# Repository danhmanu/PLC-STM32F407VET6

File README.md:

# PLC STM32F407VET6 – Modbus TCP – 16 DO transistor – 10 AI

Mạch nguyên lý KiCad 10 cho bộ PLC: điều khiển qua LAN bằng **Modbus TCP** (module W5500 Lite), nạp code qua **USB‑C (CH340C)**, 16 ngõ ra transistor cách ly quang, 10 ngõ vào analog **4–20mA**.

## Cấu trúc thư mục

| Đường dẫn | Nội dung |
|---|---|
| `kicad/PLC_STM32_Modbus.kicad_pro` | Project KiCad (mở file này) |
| `kicad/*.kicad_sch` | 6 trang mạch con (xem bảng dưới) |
| `kicad/PLC_STM32_Modbus.pdf` | Bản in PDF toàn bộ mạch |
| `kicad/BOM.csv` | Danh sách linh kiện (gom theo giá trị + footprint) |
| `kicad/erc.rpt` | Báo cáo ERC |
| `kicad/PLC_STM32_Modbus.kicad_pcb` | Mạch in 2 lớp 100×80mm |
| `kicad/fab/` | File sản xuất: Gerber + khoan (zip), file gắp đặt 2 mặt, PDF từng lớp, ảnh 3D |
| `gen/design.py`, `gen/kisch.py` | Script sinh mạch nguyên lý – sửa ở đây rồi chạy lại `sh gen/run.sh` |
| `gen/pcb.py`, `gen/finish.py`, `gen/fab.sh` | Script đặt linh kiện, nạp kết quả đi dây + đổ đồng, xuất file sản xuất |

> ⚠️ Các file `.kicad_sch` được **sinh tự động**. Nếu bạn sửa trực tiếp trong KiCad thì **đừng** chạy lại `gen/run.sh`, vì script sẽ ghi đè lên các file đó.

## Các trang mạch

| Trang | Nội dung chính |
|---|---|
| **Nguồn 24VDC** | PTC MF‑MSMF050 (0.5A/60V) → diode chống ngược SS110 → TVS SMBJ33CA → cuộn lọc common‑mode TDK ACM7060 → ferrite 3A + 47µF/10µF → **+24V**. Buck **LMR16006Y** (vào tới 60V) → 5V. Diode OR với VBUS của USB → **AMS1117‑3.3** → +3V3. Ferrite tách riêng **+3.3VA** cho ADC |
| **MCU** | STM32F407VET6, thạch anh 8MHz, **REF3030 (3.000V) làm VREF+**, nút RESET/BOOT, cổng SWD 10 chân, LED RUN/ERR |
| **USB nạp code** | USB‑C, USBLC6 chống tĩnh điện, polyfuse 500mA, **CH340C → USART1** (cổng bootloader của STM32), mạch tự vào bootloader bằng DTR/RTS (2×MMBT3904 + MMBT3906), jumper AUTO‑BOOT |
| **Ethernet** | **Module W5500 Lite** (J401, có sẵn W5500 + thạch anh + biến áp + RJ45), cắm qua 2 hàng socket 1×6. Trên board chỉ còn tụ 10µF + 100nF cho 3V3 module và 2 trở kéo lên 10k cho INT/RST – Modbus TCP |
| **16 ngõ ra transistor** | Mỗi kênh: opto **PC817 (SMD‑4, cách ly 5000 Vrms)** → **MOSFET DMN6075S (60V/2.5A)**, diode dập SS16, LED báo phía tải. Kiểu ngõ ra **sink (NPN)**: tải đấu giữa V+ và Yn |
| **10 ngõ vào analog (chỉ 4–20mA)** | Mỗi kênh: TVS SMF5.0CA, **shunt 120Ω 0.1% 25ppm**, lọc RC 4.7k/100nF vào ADC (không có cầu chì từng kênh). Cầu đấu J703 cấp nguồn 24V nuôi cảm biến 2 dây, qua PTC F711 **0.5A/60V (MF‑MSMF050‑2, gói 1812)** |

## Cách đọc sơ đồ

**Kiểu vẽ:**
- **Nối trong cùng một trang:** vẽ bằng **dây thật**. Mỗi net có một nhãn tên đặt trên dây (VIN_P, BUCK_SW, OSC_IN…) để tìm kiếm.
- **Tín hiệu đi sang trang khác:** dùng **nhãn global** (DOx, AIx_ADC, ETH_*, UART1_*, NRST, BOOT0…).
- **GND, +3V3, +24V…:** dùng power symbol.
- **Một số net vẫn giữ dạng nhãn**, vì nếu kéo dây thật sẽ phải băng ngang cả trang:
  - Hai rail ngõ ra **V24_OUT / COM_OUT** (37–53 điểm nối).
  - Một số đường **Yn** ra cầu đấu J501/J502.

**Ghi chú trên sơ đồ:**
- Ghi chú màu xanh (font Arial, tiếng Việt có dấu) đặt **ngay cạnh linh kiện / khối mà nó giải thích** (vị trí được tìm tự động để không đè lên ký hiệu, dây, nhãn):
  - Mỗi khối mạch có một tiêu đề in đậm nêu tác dụng của khối.
  - Mỗi linh kiện hoặc nhóm linh kiện có ghi chú ngắn về vai trò của nó.
  - Với 16 kênh ngõ ra và 10 kênh analog (giống nhau), ghi chú chi tiết đặt ở kênh đầu tiên.
  - **Cách tính giá trị**: dòng LED, cầu chia gate MOSFET, gợn dòng/gợn áp bộ buck, tụ tải thạch anh, điện trở shunt 4–20mA, tần số cắt bộ lọc RC, trở phối hợp Ethernet…
- Trang tổng quan (root) tóm tắt toàn hệ thống.
- Nội dung ghi chú nằm trong `gen/notes.py`; sửa ở đó rồi chạy `sh gen/run.sh` để cập nhật.

**Tìm nhanh một net trong Eeschema:**
- Bấm vào dây hoặc nhãn rồi nhấn **`** (phím dấu huyền) để tô sáng cả net.
- **View → Panels → Net Navigator** để xem danh sách mọi chân của net.
- **Ctrl+F** để tìm theo tên.

**Sinh lại sơ đồ:**
- Chạy `sh gen/run.sh`. Bộ tự đi dây nằm trong `gen/schroute.py`.
- Sau đó cập nhật liên kết PCB:
  1. Xuất netlist: `kicad-cli sch export netlist --format kicadsexpr -o gen/plc.net kicad/PLC_STM32_Modbus.kicad_sch`
  2. Chạy `gen/relink.py`.
- Đường dây trên PCB được giữ nguyên.

## Gán chân STM32F407VET6

| Chức năng | Chân |
|---|---|
| DO1…DO16 | PE1, PE0, PB9, PB8, PB7, PB6, PB5, PB4, PD7, PD6, PD5, PD4, PD3, PD2, PD1, PD0 (các chân ở cạnh trên của LQFP, hướng về khối ngõ ra để dễ đi dây) |
| AI1…AI10 | PA0, PA1, PA2, PA3, PC0, PC1, PC2, PC3, PC4, PC5 (ADC1, 12‑bit) |
| Module W5500 Lite (SPI2, tối đa 21MHz) | PB12 = CS, PB13 = SCK, PB14 = MISO, PB15 = MOSI, PD8 = RST, PD9 = INT |
| USB/CH340C (USART1) | PA9 = TX, PA10 = RX |
| SWD | PA13 = SWDIO, PA14 = SWCLK, PB3 = SWO |
| LED | PD12 = RUN, PD13 = ERR |
| Còn trống | PA4–PA8, PA11, PA12, PA15, PB0, PB1, PB10, PB11, PC6–PC15, PD10, PD11, PD14, PD15, PE2–PE15 (đã đánh dấu NC) |

## Ngõ vào analog 4–20mA – công thức đổi

- Shunt 120Ω nối thẳng vào ADC qua lọc RC (không còn cầu chia áp): `Vadc = I × 120Ω`, VREF = 3.000V.
  - 4mA → 0.48V, 20mA → 2.40V, 24mA → 2.88V.
  - Dải 4–20mA chiếm khoảng 2600 mức ADC.
  - Phát hiện được dòng lỗi theo NAMUR: < 3.8mA (đứt dây) và > 20.5mA.
- **Sụt áp trên tải ≈ 2.4V ở 20mA.** Cảm biến 2 dây cấp 24V còn khoảng 21V để hoạt động.
- **Đấu dây cảm biến:**
  - **2 dây (loop‑powered):** 24V loop (J703) → (+) cảm biến → (−) cảm biến → AIn (J701).
  - **4 dây:** ngõ ra mA của cảm biến → AIn; chân 0V của cảm biến → GND (J703).
- **Firmware:** `I(mA) = raw / 4095 × 3000 / 120`. Nên hiệu chuẩn offset/gain cho từng kênh và lưu vào Holding Register.
- **Bảo vệ:** TVS 5V kẹp xung/quá áp; trở 4.7k giới hạn dòng vào chân ADC ở khoảng 1mA.
- ⚠️ **Không có cầu chì từng kênh:** nếu đấu nhầm 24V thẳng vào chân AI, dòng 24V/120Ω = 200mA (4.8W) sẽ **cháy shunt 120Ω và TVS** của kênh đó. Chân ADC vẫn an toàn. Kiểm tra kỹ dây trước khi cấp điện.

## Ngõ ra transistor

- Phía tải có nguồn riêng: cấp 24V vào **V+ / COM** trên cầu đấu J501/J502 (chân 2 = V+, chân 1 = COM; chân 10…3 = Y1…Y8).
  - Nguồn này **cách ly** với mạch logic qua opto.
  - Nếu không cần cách ly, có thể nối chung với nguồn 24V của board.
- Khi kênh ON, gate MOSFET ≈ ½·V+ (≈ 12V). Dòng tối đa mỗi kênh khoảng 2A (giới hạn bởi tản nhiệt SOT‑23 và độ rộng đường mạch). Nên giới hạn tổng dòng mỗi nhóm 8 kênh ≤ 4A.

## Nạp chương trình qua USB

1. Cắm USB‑C. Không cần cấp 24V: board tự lấy nguồn 5V từ USB.
2. **Tự động** (cắm jumper AUTO‑BOOT JP301): phần mềm nạp điều khiển hai đường DTR/RTS theo trình tự sau (giống esptool):
   - RTS = 1, DTR = 0 → MCU bị reset.
   - RTS = 0, DTR = 1 → nhả reset trong khi BOOT0 = 1 → MCU vào bootloader UART.
   - Thả cả hai.
   - Có thể dùng `stm32flash` với tùy chọn `-i` (chuỗi GPIO DTR/RTS), hoặc script Python + pyserial.
3. **Thủ công**: giữ **BOOT**, bấm rồi nhả **RESET**, sau đó nhả BOOT. Tiếp theo nạp bằng **STM32CubeProgrammer** (UART) hoặc Arduino IDE (STM32duino, upload method “Serial”).
4. Cổng SWD (ST‑Link) để debug.

## Bảng địa chỉ Modbus TCP gợi ý (cổng 502)

| Vùng | Địa chỉ | Nội dung |
|---|---|---|
| Coils | 00001–00016 | DO1–DO16 |
| Input Registers | 30001–30010 | AI1–AI10 (raw hoặc ×100 đơn vị kỹ thuật) |
| Holding Registers | 40001+ | IP/mask/gateway, chế độ V/mA từng kênh, hệ số hiệu chuẩn, timeout an toàn cho ngõ ra |

⚠️ Modbus TCP **không có mã hóa hay xác thực**. Nếu muốn điều khiển qua Internet, hãy đi qua VPN (WireGuard/Tailscale). Không mở thẳng port 502 trên router.

## Mạch in (PCB) 2 lớp – 120 × 90 mm

**Bố trí** (nhìn từ mặt trên):
- **Cạnh trên – phía tải (cách ly):** cầu đấu ngõ ra J501/J502, bước 3.81mm. Từ trái sang phải: Y1…Y8, V+, COM | Y9…Y16, V+, COM. Ở giữa hai cầu đấu là TVS + tụ lọc nguồn relay.
- **Cạnh dưới:** J701 (AI1…AI10, 4–20mA), J703 (24V loop ×3, GND ×3), J101 (24VDC IN: +, −).
- **Cạnh trái:** USB‑C nạp code. **Cạnh phải:** module W5500 Lite, cổng LAN chĩa ra ngoài mép board (nhô ~2.5mm).
- **Bên trong:** MCU ở giữa, module Ethernet bên phải, khối nguồn ở góc dưới phải (dịch xuống 1.2mm để nhường chỗ cho module), analog ở góc dưới trái. 4 lỗ bắt vít M3 ở 4 góc.
- **Mặt dưới** chỉ có tụ/trở nhỏ (tụ lọc ngay dưới chân nguồn IC, cầu chia analog, cổng SWD) → cần **lắp ráp SMT 2 mặt**.

### Lắp module W5500 Lite

- Hàn lên board **2 hàng socket cái 1×6 (bước 2.54mm), cách nhau 20.32mm**. Module hàn header đực **chân hướng xuống** rồi cắm vào socket.
- Hướng cắm: **cổng LAN hướng ra mép phải** của board, chân vuông (pin 1 = GND) theo silkscreen.
- Dưới thân module (mặt dưới board) có C401 10µF, C402 100nF (lọc 3V3) và R401/R402 10k (kéo lên INT/RST).
- Nối dây module ↔ STM32: MOSI→PB15, SCLK→PB13, CS→PB12, MISO→PB14, INT→PD9, RST→PD8, 3V3, GND. Chân NC để trống.

### Cách ly ngõ ra – dùng với relay ngoài có nguồn riêng

- **Không cần thêm bộ cách ly.** Mỗi kênh đã có opto PC817 (cách ly 5000 Vrms) giữa MCU và MOSFET.
- **Thông số PC817 trong mạch:**
  - Dòng LED ≈ 4.5mA (3.3V qua 470Ω). Với CTR tối thiểu 50%, transistor của opto dẫn được ≥ 2.2mA, trong khi mạch kích gate chỉ cần ≈ 1.2mA.
  - Vceo của PC817 là 35V, nên **nguồn relay tối đa 30V**.
  - Nên dùng PC817 có phân hạng CTR (B/C) cho chắc chắn.
- **Footprint:** SMDIP‑4 W9.53mm (bản chân cánh, mã đuôi "S", ví dụ PC817XNNSZ0F hoặc EL817S). Mỗi kênh một opto, đặt vắt qua rãnh cách ly; khoảng cách giữa hai hàng pad ≈ 7.5mm.
- **Đấu nối:** nguồn relay **+ → V+**, **0V → COM**, cuộn relay đấu giữa **V+** và **Yn**. Diode dập SS16 đã có sẵn trên board.
- **Điện áp relay hỗ trợ: 12–30V** (gate MOSFET được phân áp ≈ ½·V+). Relay 5V không dùng được với bộ trở hiện tại.
- **Ngõ ra kiểu sink (NPN).** Nếu dùng module relay có sẵn mạch kích, chọn loại kích mức thấp / NPN.
- **Trên PCB:**
  - Có **rãnh cách ly 2.4mm** chạy ngang dưới thân 16 opto. Trong rãnh không có dây, via hay đồng trên cả 2 lớp.
  - Phía tải đổ đồng **COM_OUT**, phía logic đổ đồng **GND**. Chỉ opto bắc qua rãnh.
  - **Đừng nối COM với GND của board.** Nếu nối thì mất cách ly; mạch vẫn chạy, nhưng nhiễu từ relay sẽ lan vào mạch logic.

**Quy tắc thiết kế:**

| Nhóm net | Độ rộng dây | Khoảng cách |
|---|---|---|
| Mặc định (tín hiệu) | 0.2mm | 0.2mm |
| Supply (+3V3, +3.3VA, GND) | 0.3mm | 0.2mm |
| Power (24V, 5V, VBUS, V24_OUT, COM_OUT, Y1…Y16) | 0.8mm | 0.2mm |

- Via 0.6/0.3mm.
- Via khâu (stitching) GND và COM_OUT theo lưới 3mm.
- Dây và via cách mép board ≥ 0.45mm.

### Trạng thái đi dây – CẦN HOÀN THIỆN TRƯỚC KHI ĐẶT MẠCH

- Freerouting + script đã đi phần lớn dây. **Còn 26 kết nối** cần nối tay; danh sách ở `kicad/unrouted.txt`:
  - +3V3 (7) và GND (2) quanh chân nguồn STM32.
  - Tín hiệu: ETH_MOSI, ETH_MISO (MCU → module), UART1_RX/TX, NRST, DO1, LED_RUN, AI5/6/8_ADC.
  - USB: VBUS_C (2), CC1, VBUS. Nguồn: +24V, VIN_RAW, BUCK_CB.
- **DRC hiện tại:**
  - 0 lỗi điện (chập, khoảng cách, lỗ khoan). Không lệch so với sơ đồ nguyên lý.
  - Còn vài cảnh báo "via hở", là via fan‑out +3V3 dưới STM32, thuộc chính các kết nối +3V3 chưa nối.
  - Còn cảnh báo silkscreen (chữ chồng nhau).
- **Cách hoàn thiện:** mở `PLC_STM32_Modbus.kicad_pcb`, dùng Interactive Router (phím **X**) nối từng đường theo ratsnest. Sau đó chạy DRC cho đến khi **Unconnected = 0**.
- ⚠️ **Không gửi Gerber đi sản xuất khi DRC còn báo "unconnected".** Sau khi nối xong, chạy `sh gen/fab.sh` hoặc xuất Gerber trực tiếp trong KiCad.

### Tái tạo PCB bằng script

```bash
"/c/Program Files/KiCad/10.0/bin/python.exe" gen/pcb.py                     # đặt linh kiện + fan-out + rãnh cách ly
"/c/Program Files/KiCad/10.0/bin/python.exe" gen/finish.py gen/routing/pc817c.ses gen/routing/pc817d.ses   # nạp đường đi dây, đổ đồng, via khâu
"/c/Program Files/KiCad/10.0/bin/python.exe" gen/make_lib.py                # tạo thư viện riêng PLC (ký hiệu + footprint W5500 Lite)
"/c/Program Files/KiCad/10.0/bin/python.exe" gen/sync_pcb.py                # đồng bộ PCB theo netlist (thêm/bớt/đổi footprint)
"/c/Program Files/KiCad/10.0/bin/python.exe" gen/place_module.py kicad/PLC_STM32_Modbus.kicad_pcb   # đặt module ở mép phải
"/c/Program Files/KiCad/10.0/bin/python.exe" gen/merge_ses.py kicad/PLC_STM32_Modbus.kicad_pcb file.ses   # gộp dây đi bổ sung
"/c/Program Files/KiCad/10.0/bin/python.exe" gen/safe_clean.py              # xóa dây/via hở, tự hoàn tác nếu làm mất kết nối
"/c/Program Files/KiCad/10.0/bin/kicad-cli.exe" pcb drc --format json -o kicad/drc.json kicad/PLC_STM32_Modbus.kicad_pcb
"/c/Program Files/KiCad/10.0/bin/python.exe" gen/cleanup.py                 # xóa đoạn chập / chỉnh dây vi phạm khoảng cách (nếu có)
sh gen/fab.sh                                                                # Gerber, khoan, pos, PDF, ảnh 3D
```

> ⚠️ Chạy lại `gen/pcb.py` hoặc `gen/finish.py` sẽ **ghi đè** những chỉnh sửa đó và phần đi dây tay của bạn. Bản 100×80 cũ được lưu ở `gen/pcb_100x80.py.bak`.

## Kết quả kiểm tra

- **ERC: còn 1 cảnh báo, là cố ý.** Chân `V3` của CH340C (kiểu power‑output trong thư viện) nối vào +3V3; datasheet yêu cầu như vậy khi VCC = 3.3V.
- Đã kiểm tra netlist: không có net nào chỉ có một chân. Các net DO, AI, SPI, UART, NRST, BOOT0 và mạch trong từng kênh nối đúng.

## Việc cần kiểm tra / làm tiếp trước khi làm PCB

1. **Module W5500 Lite (J401)**: footprint tự vẽ `PLC:W5500_Lite_Module` theo bản vẽ 23×25mm (2 hàng 1×6, bước 2.54mm, hai hàng cách nhau 20.32mm). **In footprint tỉ lệ 1:1 và đặt module thật lên để đối chiếu** trước khi đặt mạch. Module cấp nguồn 3.3V (W5500 + PHY ≈ 130–150mA).
2. **Cuộn lọc common‑mode**: TDK ACM7060‑701‑2PL. Kiểm tra lại dòng định mức và thứ tự chân 1‑2 / 3‑4 khớp footprint.
3. **Cuộn cảm buck**: 10µH cho LMR16006Y (2.1MHz). Đối chiếu lại bảng chọn L/C trong datasheet TI.
4. Footprint của các linh kiện dùng ký hiệu chung (R, C, LED, polyfuse…) đã gán sẵn (0603/0805/1206). Shunt 120Ω tiêu tán 48mW ở 20mA (đã chọn 1206 0.1% 25ppm để ổn định nhiệt).
5. Chưa có ngõ vào số (DI). Nếu cần, còn trống PE2–PE14 cho 13 DI cách ly quang.

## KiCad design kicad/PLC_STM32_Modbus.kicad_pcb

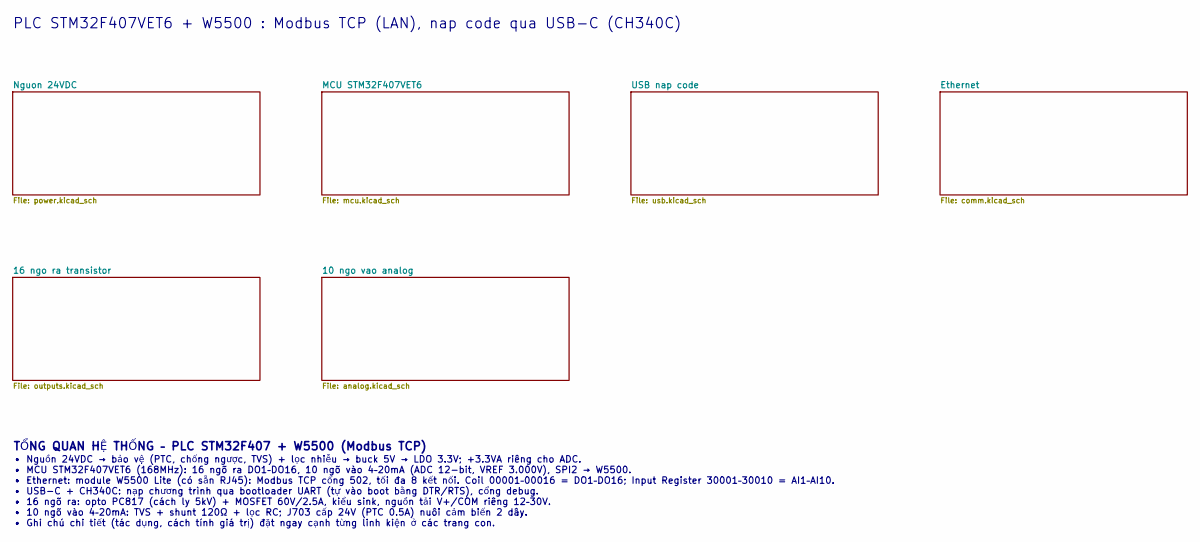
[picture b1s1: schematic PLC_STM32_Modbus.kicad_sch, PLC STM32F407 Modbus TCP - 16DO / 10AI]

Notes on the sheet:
PLC STM32F407VET6 + W5500 : Modbus TCP (LAN), nap code qua USB-C (CH340C)
TỔNG QUAN HỆ THỐNG – PLC STM32F407 + W5500 (Modbus TCP)
• Nguồn 24VDC → bảo vệ (PTC, chống ngược, TVS) + lọc nhiễu → buck 5V → LDO 3.3V; +3.3VA riêng cho ADC. • MCU STM32F407VET6 (168MHz): 16 ngõ ra DO1–DO16, 10 ngõ vào 4–20mA (ADC 12-bit, VREF 3.000V), SPI2 → W5500. • Ethernet: module W5500 Lite (có sẵn RJ45): Modbus TCP cổng 502, tối đa 8 kết nối. Coi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

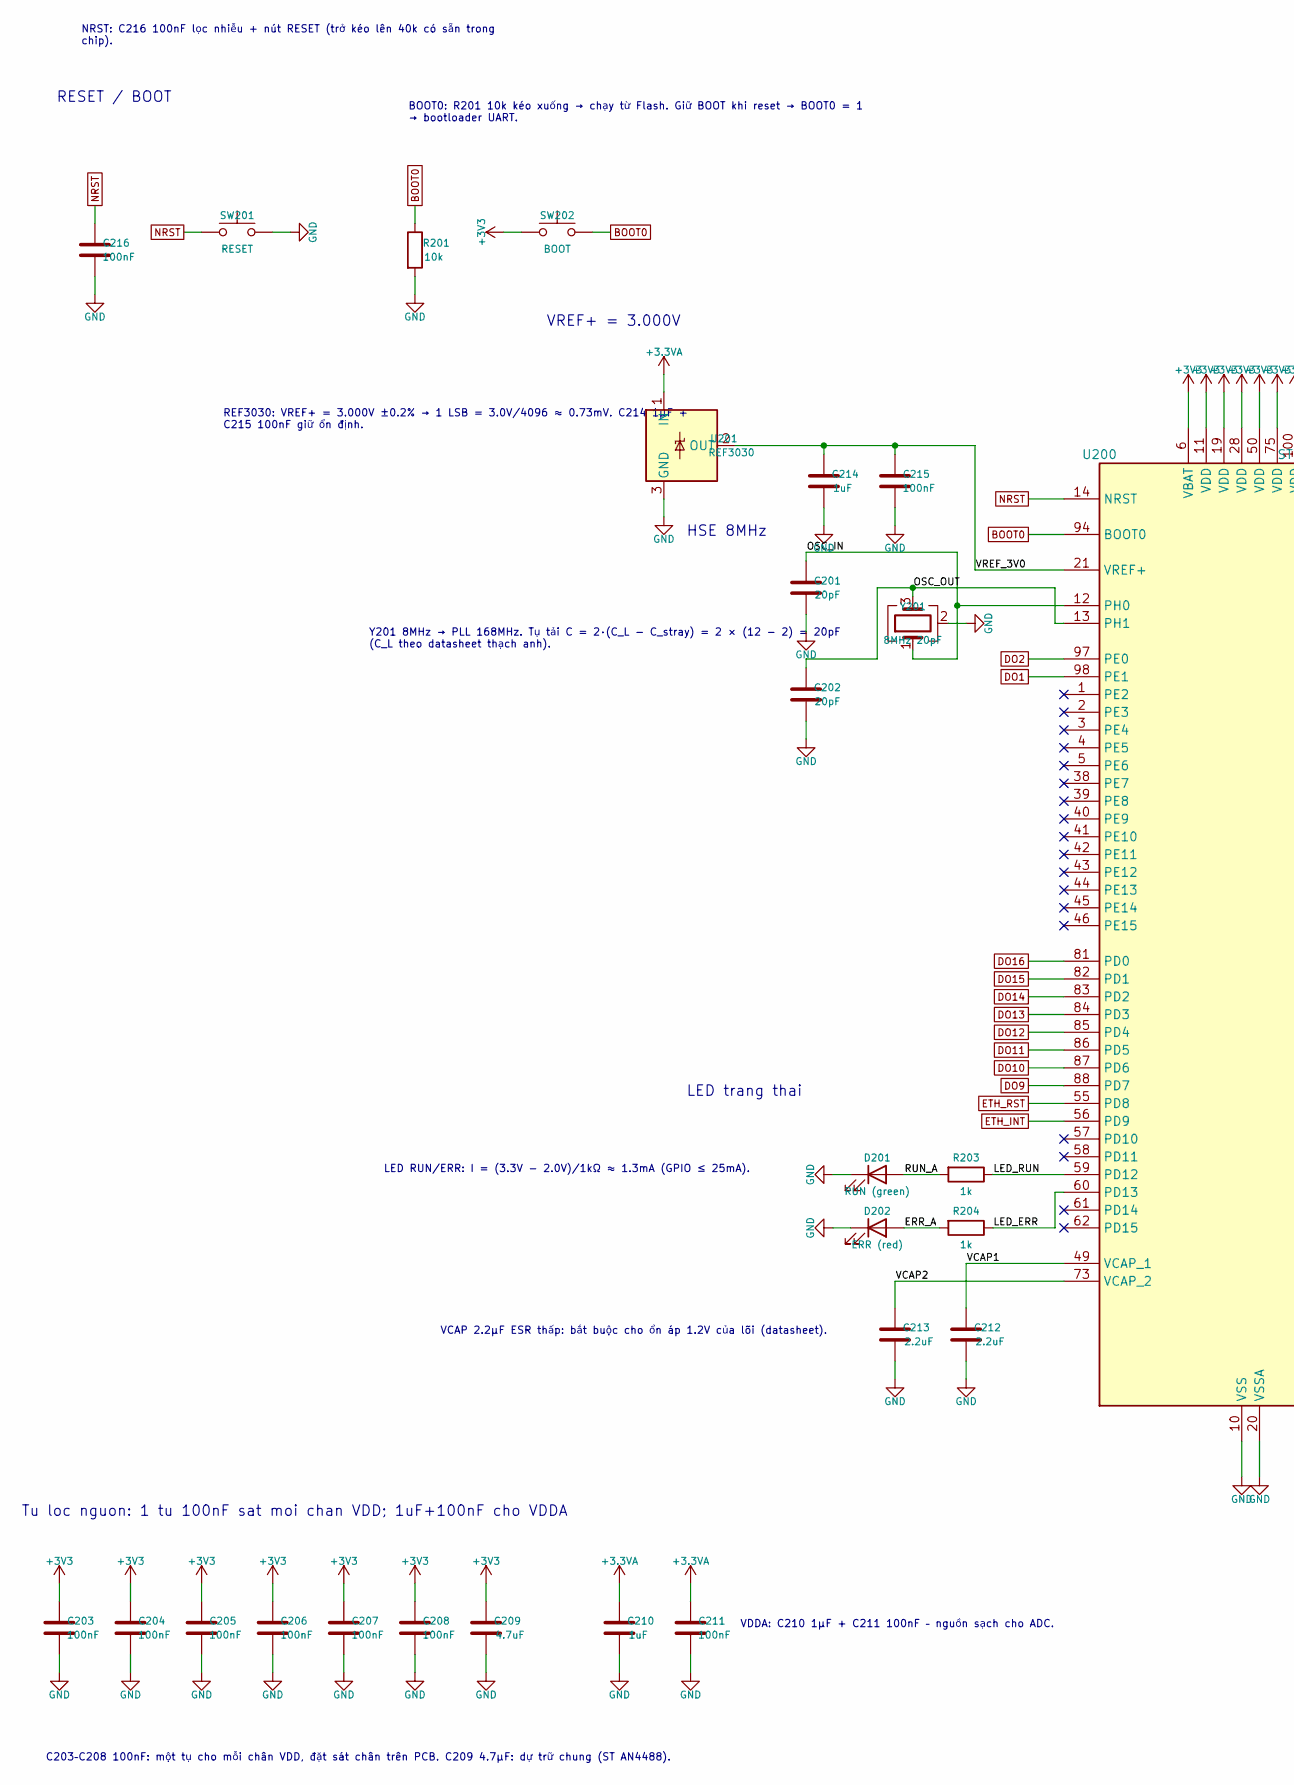
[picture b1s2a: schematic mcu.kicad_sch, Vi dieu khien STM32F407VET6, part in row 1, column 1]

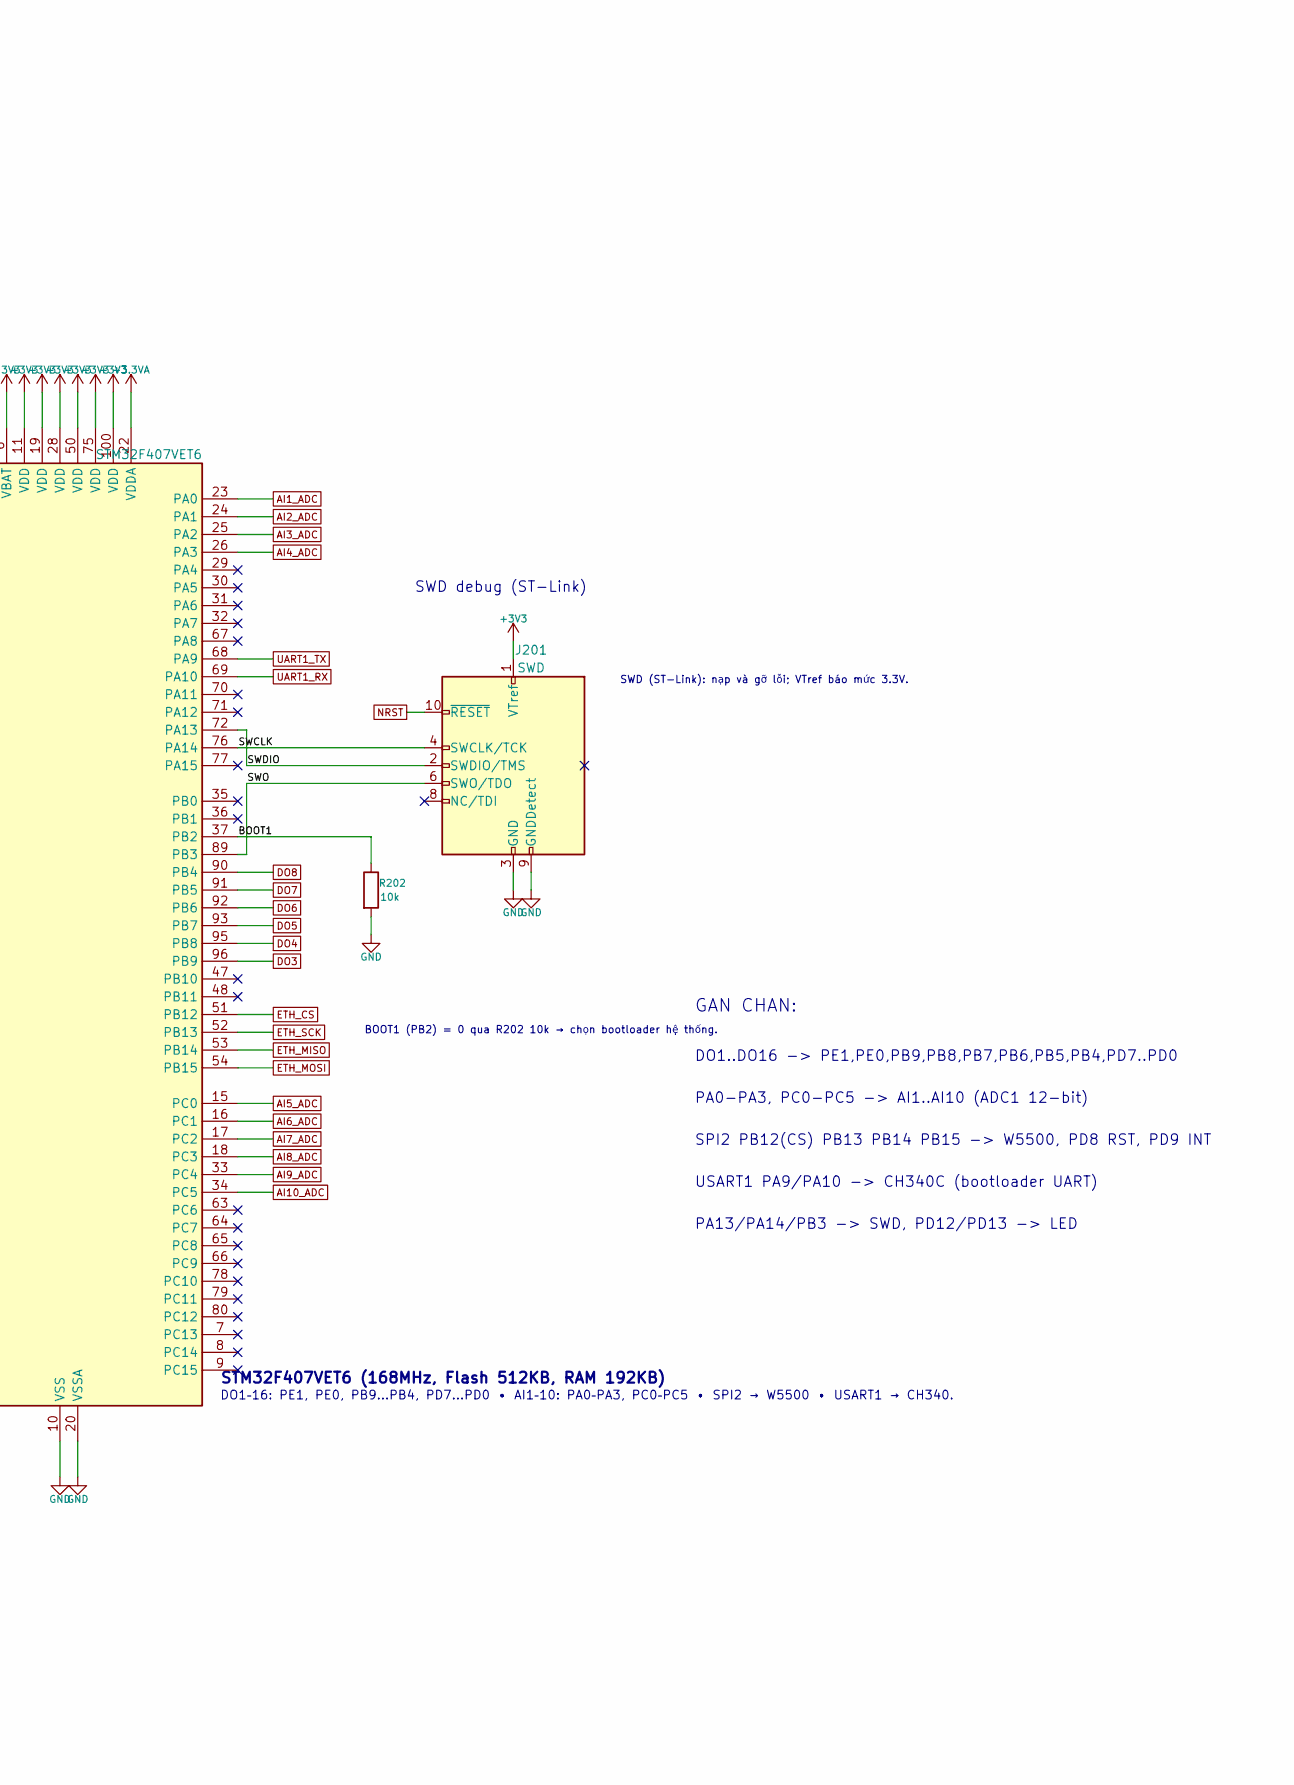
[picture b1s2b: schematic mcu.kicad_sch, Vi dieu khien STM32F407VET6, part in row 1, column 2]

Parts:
C201, C202: 20pF; C_0603_1608Metric
C203, C204, C205, C206, C207, C208, C211, C215, C216: 100nF; C_0603_1608Metric
C209: 4.7uF; C_0805_2012Metric
C210, C214: 1uF; C_0603_1608Metric
C212, C213: 2.2uF; C_0805_2012Metric
D201: RUN (green); LED_0603_1608Metric
D202: ERR (red); LED_0603_1608Metric
J201: SWD; PinHeader_2x05_P1.27mm_Vertical_SMD
R201, R202: 10k; R_0603_1608Metric
R203, R204: 1k; R_0603_1608Metric
SW201: RESET; SW_SPST_PTS810
SW202: BOOT; SW_SPST_PTS810
U200: STM32F407VET6; LQFP-100_14x14mm_P0.5mm
U201: REF3030; SOT-23
Y201: 8MHz 20pF; Crystal_SMD_3225-4Pin_3.2x2.5mm

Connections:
+3.3VA: C210.1, C211.1, U200.22 (VDDA), U201.1 (IN); also elsewhere on the board
+3V3: C203.1, C204.1, C205.1, C206.1, C207.1, C208.1, C209.1, J201.1 (VTref), SW202.1, U200.6 (VBAT), U200.11 (VDD), U200.19 (VDD), U200.28 (VDD), U200.50 (VDD), U200.75 (VDD), U200.100 (VDD); also elsewhere on the board
/MCU STM32F407VET6/BOOT1: R202.1, U200.37 (PB2)
/MCU STM32F407VET6/ERR_A: D202.2 (A), R204.2
/MCU STM32F407VET6/LED_ERR: R204.1, U200.60 (PD13)
/MCU STM32F407VET6/LED_RUN: R203.1, U200.59 (PD12)
/MCU STM32F407VET6/OSC_IN: C201.1, U200.12 (PH0), Y201.1
/MCU STM32F407VET6/OSC_OUT: C202.1, U200.13 (PH1), Y201.3
/MCU STM32F407VET6/RUN_A: D201.2 (A), R203.2
/MCU STM32F407VET6/SWCLK: J201.4 (SWCLK/TCK), U200.76 (PA14)
/MCU STM32F407VET6/SWDIO: J201.2 (SWDIO/TMS), U200.72 (PA13)
/MCU STM32F407VET6/SWO: J201.6 (SWO/TDO), U200.89 (PB3)
/MCU STM32F407VET6/VCAP1: C212.1, U200.49 (VCAP_1)
/MCU STM32F407VET6/VCAP2: C213.1, U200.73 (VCAP_2)
/MCU STM32F407VET6/VREF_3V0: C214.1, C215.1, U200.21 (VREF+), U201.2 (OUT)
AI1_ADC: U200.23 (PA0); also elsewhere on the board
AI2_ADC: U200.24 (PA1); also elsewhere on the board
AI3_ADC: U200.25 (PA2); also elsewhere on the board
AI4_ADC: U200.26 (PA3); also elsewhere on the board
AI5_ADC: U200.15 (PC0); also elsewhere on the board
AI6_ADC: U200.16 (PC1); also elsewhere on the board
AI7_ADC: U200.17 (PC2); also elsewhere on the board
AI8_ADC: U200.18 (PC3); also elsewhere on the board
AI9_ADC: U200.33 (PC4); also elsewhere on the board
AI10_ADC: U200.34 (PC5); also elsewhere on the board
BOOT0: R201.1, SW202.2, U200.94 (BOOT0); also elsewhere on the board
DO1: U200.98 (PE1); also elsewhere on the board
DO2: U200.97 (PE0); also elsewhere on the board
DO3: U200.96 (PB9); also elsewhere on the board
DO4: U200.95 (PB8); also elsewhere on the board
DO5: U200.93 (PB7); also elsewhere on the board
DO6: U200.92 (PB6); also elsewhere on the board
DO7: U200.91 (PB5); also elsewhere on the board
DO8: U200.90 (PB4); also elsewhere on the board
DO9: U200.88 (PD7); also elsewhere on the board
DO10: U200.87 (PD6); also elsewhere on the board
DO11: U200.86 (PD5); also elsewhere on the board
DO12: U200.85 (PD4); also elsewhere on the board
DO13: U200.84 (PD3); also elsewhere on the board
DO14: U200.83 (PD2); also elsewhere on the board
DO15: U200.82 (PD1); also elsewhere on the board
DO16: U200.81 (PD0); also elsewhere on the board
ETH_CS: U200.51 (PB12); also elsewhere on the board
ETH_INT: U200.56 (PD9); also elsewhere on the board
ETH_MISO: U200.53 (PB14); also elsewhere on the board
ETH_MOSI: U200.54 (PB15); also elsewhere on the board
ETH_RST: U200.55 (PD8); also elsewhere on the board
ETH_SCK: U200.52 (PB13); also elsewhere on the board
GND: C201.2, C202.2, C203.2, C204.2, C205.2, C206.2, C207.2, C208.2, C209.2, C210.2, C211.2, C212.2, C213.2, C214.2, C215.2, C216.2, D201.1 (K), D202.1 (K), J201.3 (GND), J201.5 (GND), J201.9 (GNDDetect), R201.2, R202.2, SW201.2, U200.10 (VSS), U200.20 (VSSA), U200.27 (VSS), U200.74 (VSS), U200.99 (VSS), U201.3 (GND), Y201.2 (G), Y201.4 (G); also elsewhere on the board
NRST: C216.1, J201.10 (~RESET), SW201.1, U200.14 (NRST); also elsewhere on the board
UART1_RX: U200.69 (PA10); also elsewhere on the board
UART1_TX: U200.68 (PA9); also elsewhere on the board

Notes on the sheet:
VDDA: C210 1µF + C211 100nF – nguồn sạch cho ADC.
DO1..DO16 -> PE1,PE0,PB9,PB8,PB7,PB6,PB5,PB4,PD7..PD0
BOOT1 (PB2) = 0 qua R202 10k → chọn bootloader hệ thống.
STM32F407VET6 (168MHz, Flash 512KB, RAM 192KB)
LED RUN/ERR: I = (3.3V − 2.0V)/1kΩ ≈ 1.3mA (GPIO ≤ 25mA).
REF3030: VREF+ = 3.000V ±0.2% → 1 LSB = 3.0V/4096 ≈ 0.73mV. C214 1µF + C215 100nF giữ ổn định.
BOOT0: R201 10k kéo xuống → chạy từ Flash. Giữ BOOT khi reset → BOOT0 = 1 → bootloader UART.
RESET / BOOT
NRST: C216 100nF lọc nhiễu + nút RESET (trở kéo lên 40k có sẵn trong chip).
PA13/PA14/PB3 -> SWD, PD12/PD13 -> LED
DO1–16: PE1, PE0, PB9…PB4, PD7…PD0 • AI1–10: PA0–PA3, PC0–PC5 • SPI2 → W5500 • USART1 → CH340.
USART1 PA9/PA10 -> CH340C (bootloader UART)
Y201 8MHz → PLL 168MHz. Tụ tải C = 2·(C_L − C_stray) = 2 × (12 − 2) = 20pF (C_L theo datasheet thạch anh).
VREF+ = 3.000V
Tu loc nguon: 1 tu 100nF sat moi chan VDD; 1uF+100nF cho VDDA
C203–C208 100nF: một tụ cho mỗi chân VDD, đặt sát chân trên PCB. C209 4.7µF: dự trữ chung (ST AN4488).
HSE 8MHz
GAN CHAN:
SWD debug (ST-Link)
VCAP 2.2µF ESR thấp: bắt buộc cho ổn áp 1.2V của lõi (datasheet).
PA0-PA3, PC0-PC5 -> AI1..AI10 (ADC1 12-bit)
SWD (ST-Link): nạp và gỡ lỗi; VTref báo mức 3.3V.
LED trang thai
SPI2 PB12(CS) PB13 PB14 PB15 -> W5500, PD8 RST, PD9 INT

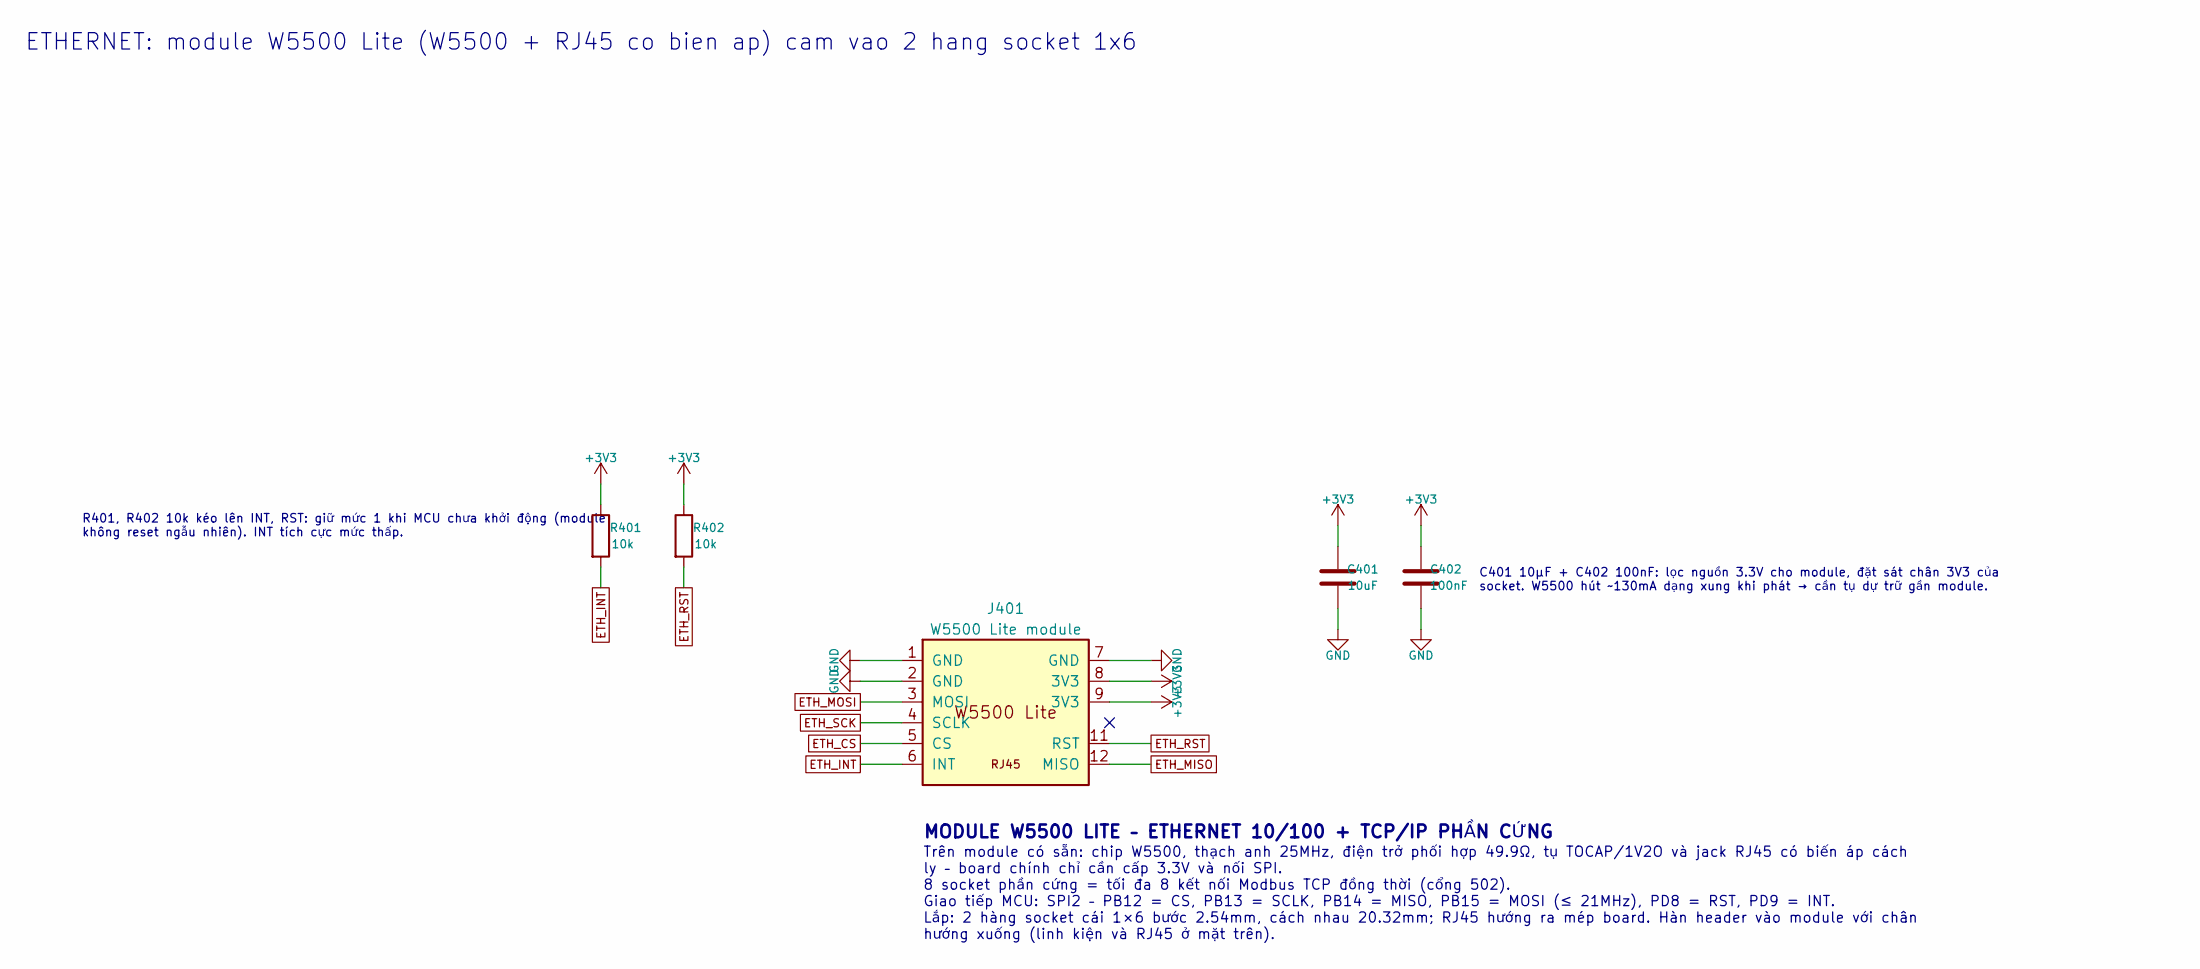
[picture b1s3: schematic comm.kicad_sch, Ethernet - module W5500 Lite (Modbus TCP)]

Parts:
C401: 10uF; C_0805_2012Metric
C402: 100nF; C_0603_1608Metric
J401: W5500 Lite module; W5500_Lite_Module
R401, R402: 10k; R_0603_1608Metric

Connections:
+3V3: C401.1, C402.1, J401.8 (3V3), J401.9 (3V3), R401.1, R402.1; also elsewhere on the board
ETH_CS: J401.5 (CS); also elsewhere on the board
ETH_INT: J401.6 (INT), R401.2; also elsewhere on the board
ETH_MISO: J401.12 (MISO); also elsewhere on the board
ETH_MOSI: J401.3 (MOSI); also elsewhere on the board
ETH_RST: J401.11 (RST), R402.2; also elsewhere on the board
ETH_SCK: J401.4 (SCLK); also elsewhere on the board
GND: C401.2, C402.2, J401.1 (GND), J401.2 (GND), J401.7 (GND); also elsewhere on the board

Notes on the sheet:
MODULE W5500 LITE – ETHERNET 10/100 + TCP/IP PHẦN CỨNG
C401 10µF + C402 100nF: lọc nguồn 3.3V cho module, đặt sát chân 3V3 của socket. W5500 hút ~130mA dạng xung khi phát → cần tụ dự trữ gần module.
R401, R402 10k kéo lên INT, RST: giữ mức 1 khi MCU chưa khởi động (module không reset ngẫu nhiên). INT tích cực mức thấp.
ETHERNET: module W5500 Lite (W5500 + RJ45 co bien ap) cam vao 2 hang socket 1x6
Trên module có sẵn: chip W5500, thạch anh 25MHz, điện trở phối hợp 49.9Ω, tụ TOCAP/1V2O và jack RJ45 có biến áp cách ly – board chính chỉ cần cấp 3.3V và nối SPI. 8 socket phần cứng = tối đa 8 kết nối Modbus TCP đồng thời (cổng 502). Giao tiếp MCU: SPI2 – PB12 = CS, PB13 = SCLK, PB14 = MISO, PB15 =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
